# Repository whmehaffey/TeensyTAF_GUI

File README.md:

# TeensyTAF_GUI

TeensyTAF version (https://github.com/whmehaffey/Teensy3.6TAF) w/ Python GUI and a slightly improved audio buffer. 

GUI is pretty simple (set/load config files, plots recent FFs and threshold matches as histograms, and lets you set a few variable on the fly (the buttons left on during running). If buttons are off during running, you can't. It will grab the FFT number and samplign rate from the Teensy, but will not let you set them in the software (you'll have to change the variable in the .ino file and then re-upload it to the teensy). This is just there so that it's saved to a config file. 

On running, saves a config file with all the variables, then writes FF, distance from target, and trial mode (HIT=0 for catch, HIT=1 for hit, and HIT=3 is the flag is set (for, e.g. interleaved DIR trials, so they can be tagged). 

Templates should be in the format in test.TEMPLT, and half the size the FFT window. 

It will also automatically update the FF threshold to maintain 75% hit rates, this value is ratcheted, and will only go up, or down, depending on the direction of training (set with Hit Above/Hit Below). 

Compilation of the Arduino code requires installing the AgileWare circular buffer libraries (Arduino menu, Sketch->Include Library->Manage Library, then search for Circular Buffer and install it). 

Python GUI was written in Python 2.7, and requires the following Python packages (installable through pip): PySerial, PyQT, numpy, pyQTgraph.

-----------------
As before, 
You can order boards at OSH Park:

https://oshpark.com/shared_projects/d7Odnek7

for ~10$ea.

or submit the eagle .brd file in the original commit (https://github.com/whmehaffey/Teensy3.6TAF) yourself.

for 44.1Khz, I recomment overclocking- otherwise it could have issues from time to time. 216MHz seems to work well. To get at it, you may have to edit boards.txt (arduino/hardware/teensy/avr/boards.txt) and uncomment the higher overclock speeds.

Once you have a template, you can recomment export_mags, and uncomment Serial.println(dp) which will export the distance between the template and the current PSD. If you're well-targeted, you should see a sharp peak, which makes it easy to set a threshold (DPTHRESH).

You can also use negative values in the template if you want to penalize spectral information that's present in a syllable you want to avoid, but absent in the target syllable.

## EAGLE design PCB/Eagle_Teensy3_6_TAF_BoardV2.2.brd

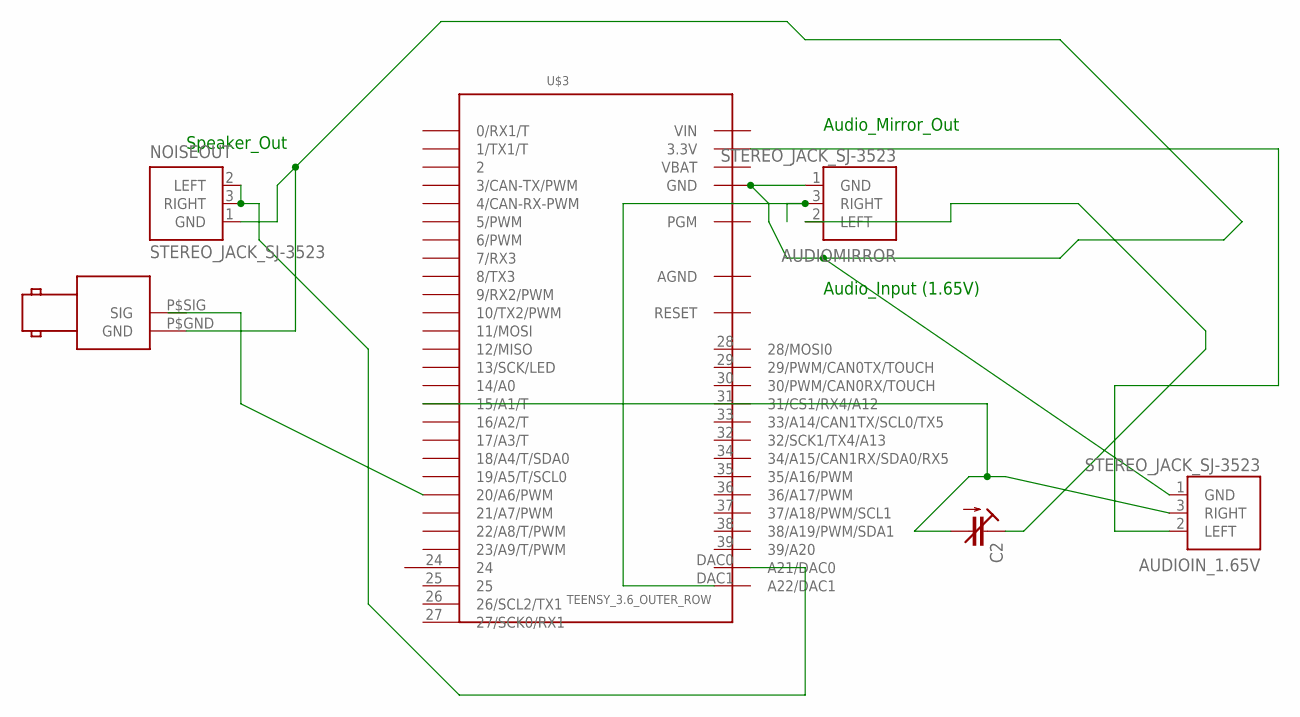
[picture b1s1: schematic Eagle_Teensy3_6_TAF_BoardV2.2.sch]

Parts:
AUDIOIN_1.65V: STEREO_JACK_SJ-3523; SJ-3523
AUDIOMIRROR: STEREO_JACK_SJ-3523; SJ-3523
C2: C-TRIMM3008; 3008
NOISEOUT: STEREO_JACK_SJ-3523; SJ-3523
TTL: BNC_RIGHT_ANGLE
U$3: TEENSY_3.6_OUTER_ROW; TEENSY3_6-OUTER_ROW

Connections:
AGND: U$3.AGND
unnamed: NOISEOUT.2 (LEFT), NOISEOUT.3 (RIGHT)
unnamed: AUDIOIN_1.65V.1 (GND), AUDIOMIRROR.1 (GND), NOISEOUT.1 (GND), TTL.P$GND (GND), U$3.3.3V2 (GND), U$3.GND, U$3.GND1 (GND), U$3.GND2 (GND)
unnamed: AUDIOIN_1.65V.2 (LEFT), U$3.3.3V, U$3.3.3V1 (3.3V)
unnamed: AUDIOIN_1.65V.3 (RIGHT), C2.- (A), U$3.15/A1 (15/A1/T)
unnamed: AUDIOMIRROR.3 (RIGHT), U$3.DAC1 (A22/DAC1)
unnamed: AUDIOMIRROR.2 (LEFT), C2.+ (E)
VBAT: U$3.VBAT
VIN: U$3.VIN

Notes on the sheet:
Speaker_Out
Audio_Mirror_Out
Audio_Input (1.65V)

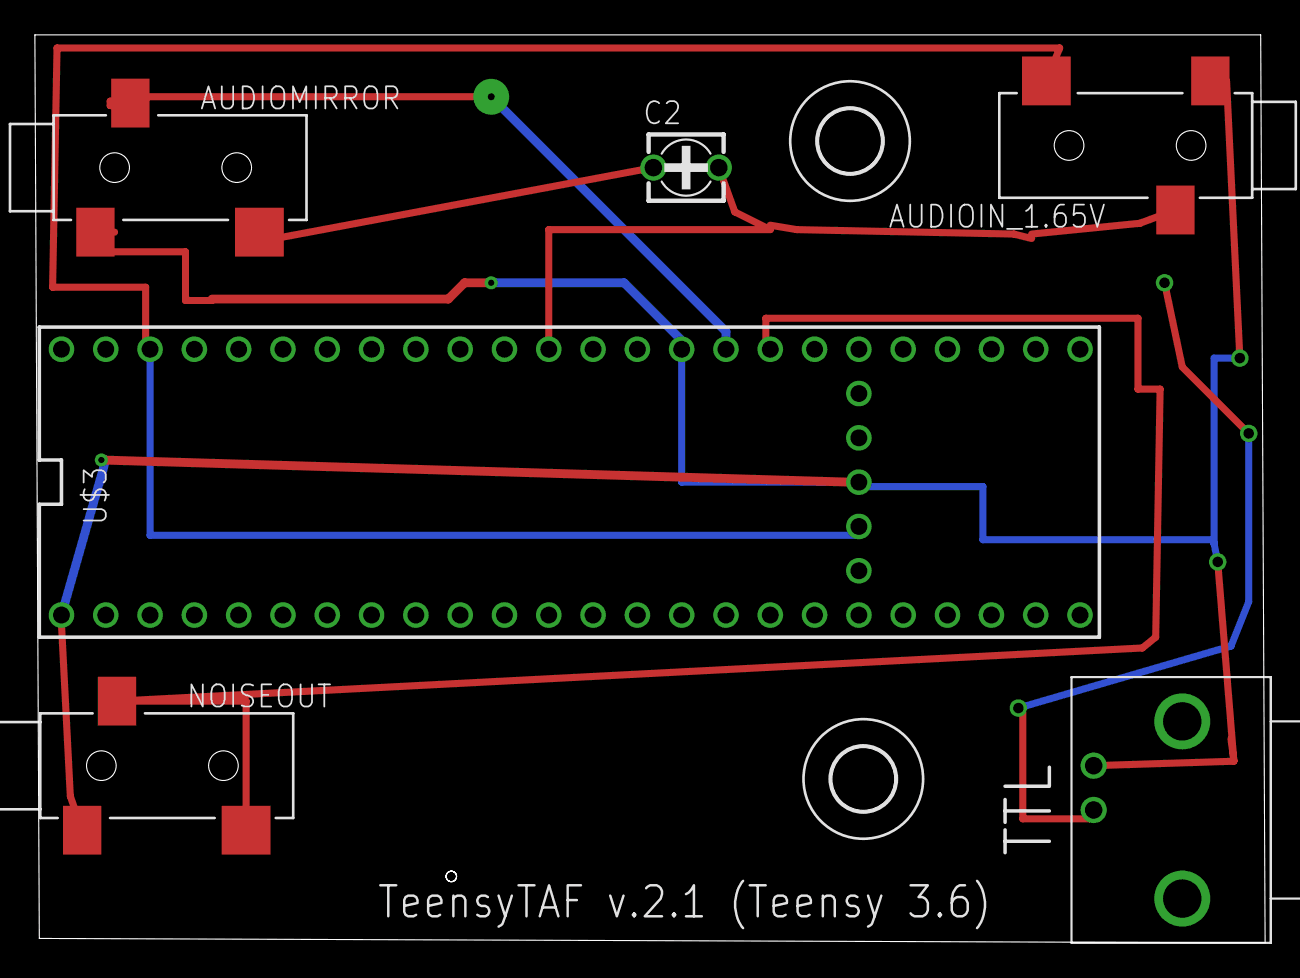
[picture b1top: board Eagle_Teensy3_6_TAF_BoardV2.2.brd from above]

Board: 2 copper layers, 70.5 x 52.1 mm, 8 parts (0 on the bottom side), 6 nets.

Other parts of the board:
U$1, U$2: 3,6

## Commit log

2019-01-02 First Commit
    First Commit.
2019-01-03 1/2/2019
    Updated Catch Trials Etc
2019-01-03 1/2/2019
    Tidied up code. Renamed example CONFIG and TEMPLATE files.
2019-01-03 1/3/2019
    Some Typos, removed some commented debugging code.
2019-01-10 Documentation, PCBs added
